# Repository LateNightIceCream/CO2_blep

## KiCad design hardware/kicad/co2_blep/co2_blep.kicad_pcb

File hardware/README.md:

# Hardware!

## Supply
- CR3032 3V cell

## Microcontroller
- using Tiny85
  - works up to VCC = 6V
- this dev-board (because I have that laying around):
  - 
- bridge LDO Regulator

## BME680
- this breakout board:
  - 

  - compatible with others, too

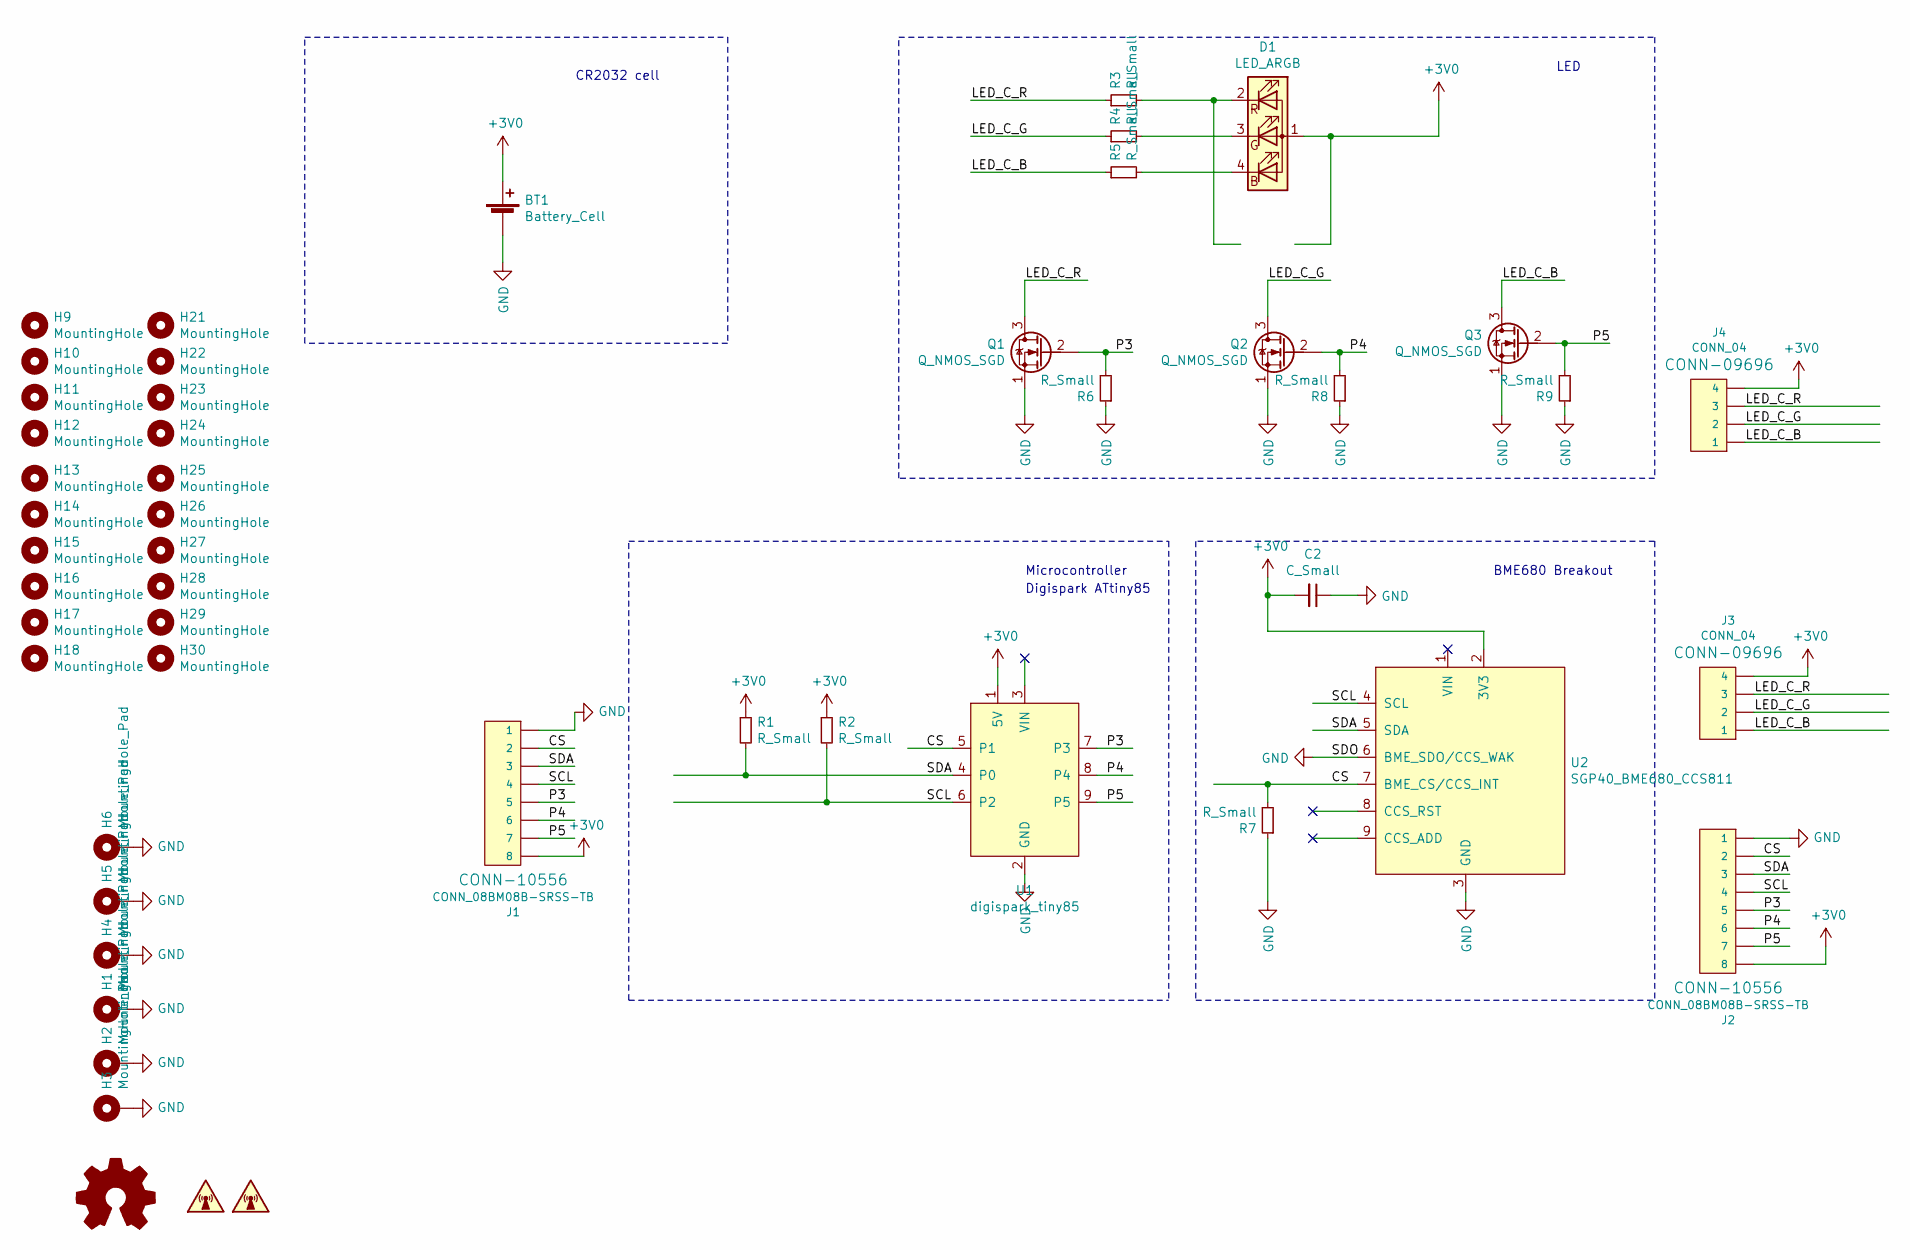
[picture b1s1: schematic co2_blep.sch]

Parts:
BT1: Battery_Cell; 2032_holder
C2: C_Small; C_Rect_L7.0mm_W2.0mm_P5.00mm
D1: LED_ARGB; led1
H1, H2, H3, H4, H5, H6: MountingHole_Pad; MountingHole_2.2mm_M2_ISO7380_Pad
H9, H10, H11, H12, H13, H14, H15, H16, H17, H18, H21, H22, H23, H24, H25, H26, H27, H28, H29, H30: MountingHole; 0.8mm_hole
J1, J2: CONN_08BM08B-SRSS-TB; PinHeader_1x08_P2.54mm_Vertical
J3, J4: CONN_04; PinHeader_1x04_P2.54mm_Vertical
Q1, Q2, Q3: Q_NMOS_SGD; TO-92
R1, R2, R3, R4, R5, R7, R8: R_Small; R_Axial_DIN0207_L6.3mm_D2.5mm_P10.16mm_Horizontal
R6, R9: R_Small; R_Axial_DIN0204_L3.6mm_D1.6mm_P2.54mm_Vertical
U1: digispark_tiny85
U2: SGP40_BME680_CCS811; sgp40_bme680_ccs811

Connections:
+3V0: BT1.1 (+), C2.2, D1.1 (A), J1.8, J2.8, J3.4, J4.4, R1.1, R2.1, U1.1 (5V), U2.2 (3V3)
/CS: J1.2, J2.2, R7.2, U1.5 (P1), U2.7 (BME_CS/CCS_INT)
/LED_C_B: J3.1, J4.1, Q3.3 (D), R5.1
/LED_C_G: J3.2, J4.2, Q2.3 (D), R4.1
/LED_C_R: J3.3, J4.3, Q1.3 (D), R3.1
/P3: J1.5, J2.5, Q1.2 (G), R6.2, U1.7 (P3)
/P4: J1.6, J2.6, Q2.2 (G), R8.2, U1.8 (P4)
/P5: J1.7, J2.7, Q3.2 (G), R9.2, U1.9 (P5)
/SCL: J1.4, J2.4, R2.2, U1.6 (P2), U2.4 (SCL)
/SDA: J1.3, J2.3, R1.2, U1.4 (P0), U2.5 (SDA)
GND: BT1.2 (-), C2.1, H1.1, H2.1, H3.1, H4.1, H5.1, H6.1, J1.1, J2.1, Q1.1 (S), Q2.1 (S), Q3.1 (S), R6.1, R7.1, R8.1, R9.1, U1.2 (GND), U2.3 (GND), U2.6 (BME_SDO/CCS_WAK)
unnamed: D1.2 (RK), R3.2
unnamed: D1.3 (GK), R4.2
unnamed: D1.4 (BK), R5.2

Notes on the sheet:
BME680 Breakout
CR2032 cell
LED
Microcontroller
Digispark ATtiny85

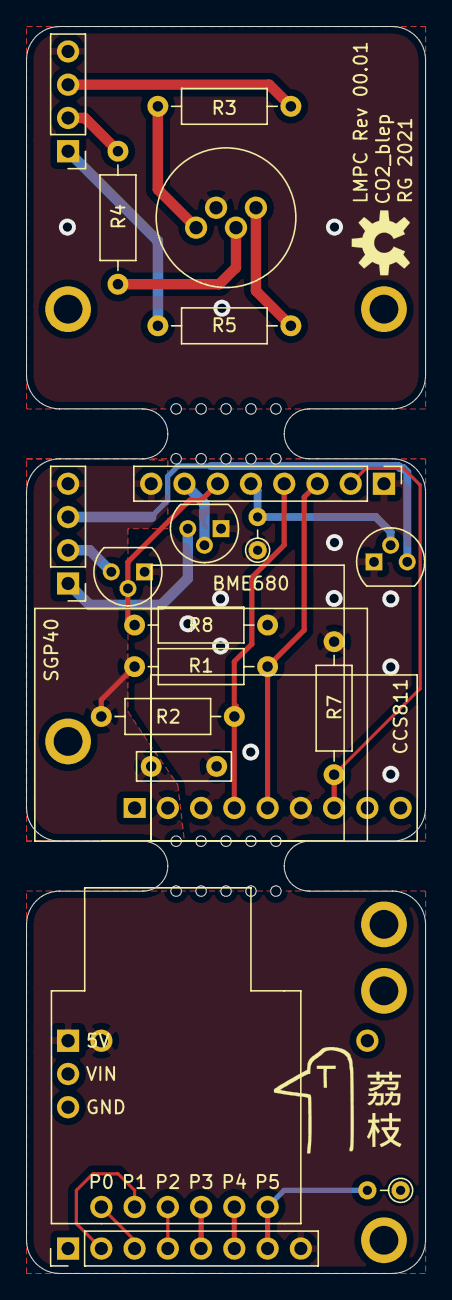
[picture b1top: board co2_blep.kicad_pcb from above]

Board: 2 copper layers, 30.5 x 95.2 mm, 47 parts (1 on the bottom side), 14 nets.

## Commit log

2021-12-05 init
